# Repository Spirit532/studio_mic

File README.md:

<div align="right">
  <details>
    <summary >🌐 Language</summary>
    <div>
      <div align="center">
        <a href="https://openaitx.github.io/view.html?user=Spirit532&project=studio_mic&lang=en">English</a>
        | <a href="https://openaitx.github.io/view.html?user=Spirit532&project=studio_mic&lang=zh-CN">简体中文</a>
        | <a href="https://openaitx.github.io/view.html?user=Spirit532&project=studio_mic&lang=zh-TW">繁體中文</a>
        | <a href="https://openaitx.github.io/view.html?user=Spirit532&project=studio_mic&lang=ja">日本語</a>
        | <a href="https://openaitx.github.io/view.html?user=Spirit532&project=studio_mic&lang=ko">한국어</a>
        | <a href="https://openaitx.github.io/view.html?user=Spirit532&project=studio_mic&lang=hi">हिन्दी</a>
        | <a href="https://openaitx.github.io/view.html?user=Spirit532&project=studio_mic&lang=th">ไทย</a>
        | <a href="https://openaitx.github.io/view.html?user=Spirit532&project=studio_mic&lang=fr">Français</a>
        | <a href="https://openaitx.github.io/view.html?user=Spirit532&project=studio_mic&lang=de">Deutsch</a>
        | <a href="https://openaitx.github.io/view.html?user=Spirit532&project=studio_mic&lang=es">Español</a>
        | <a href="https://openaitx.github.io/view.html?user=Spirit532&project=studio_mic&lang=it">Italiano</a>
        | <a href="https://openaitx.github.io/view.html?user=Spirit532&project=studio_mic&lang=ru">Русский</a>
        | <a href="https://openaitx.github.io/view.html?user=Spirit532&project=studio_mic&lang=pt">Português</a>
        | <a href="https://openaitx.github.io/view.html?user=Spirit532&project=studio_mic&lang=nl">Nederlands</a>
        | <a href="https://openaitx.github.io/view.html?user=Spirit532&project=studio_mic&lang=pl">Polski</a>
        | <a href="https://openaitx.github.io/view.html?user=Spirit532&project=studio_mic&lang=ar">العربية</a>
        | <a href="https://openaitx.github.io/view.html?user=Spirit532&project=studio_mic&lang=fa">فارسی</a>
        | <a href="https://openaitx.github.io/view.html?user=Spirit532&project=studio_mic&lang=tr">Türkçe</a>
        | <a href="https://openaitx.github.io/view.html?user=Spirit532&project=studio_mic&lang=vi">Tiếng Việt</a>
        | <a href="https://openaitx.github.io/view.html?user=Spirit532&project=studio_mic&lang=id">Bahasa Indonesia</a>
        | <a href="https://openaitx.github.io/view.html?user=Spirit532&project=studio_mic&lang=as">অসমীয়া</
      </div>
    </div>
  </details>
</div>

# Simple, high quality condenser microphone for under $100

I needed a good quality microphone, but all of the options available were either a bit pricy or just not really good in performance, so I decided to build my own.

The microphone build uses a clone RK12/CK12 capsule($40-50 on Aliexpress/Ebay/etc, search for "edge terminated capsule"), a U87 donor body($15-30, also Aliexpress, search term "U87 mic"), and a custom preamp board($20-30, this project).

The board is very simple, yet high performance - it uses a dual FET input opamp in a single package to both convert the capsule's impedance and provide a differential signal, while the bias is provided by a slightly cursed hex schmitt trigger inverter charge pump.

With the setup pictured below, the results are, to the non-audiophool ear, perfect. There is practically no self-noise due to the simplicity of the circuit and performance of the chosen opamp, plenty of dynamic range, and no signal distortion/"coloration". You get exactly what the capsule sees on the XLR connector.

#### Notes about component choice
  1. You can use pretty much any FET input opamp, **however** you must pay close attention to the quiescent current. This circuit uses a fairly high impedance power path, and the phantom power standard can't provide much current in the first place. Total power consumption of the two opamps should be no more than ~7-8mA(3.5-4mA per).

  2. Same goes for the hex inverter in terms of power consumption, but otherwise anything will do. You can substitute the part with any 40106 clone of similar functionality.
  
  3. Take care to purchase high voltage rated capacitors where specified - this is important! Ceramic capacitors lose capacitance at higher voltages, so X7R class caps rated at 100V or more are preferred(this won't explicitly solve derating, but it will help). All values are  readily available in 0805 size, so it's not an issue.

  4. Choose NP0/C0G capacitors for ceramics if your budget allows. They'll improve performance a little bit, but not by a whole lot. (this will solve derating, but at significant cost)
  
The design is licensed under the MIT license. If you want to build it, go ahead. If you want to sell it, also go ahead, but just mention this page or something. Pretty much none of this is really original and has been done dozens of times(i.e. DJJules/Sound Sleuth over at Instructables, whose circuit I took inspiration from), I just put my own twist on it.

#### Important note about cheap donor bodies
Most cheap donor bodies will come pre-anodized or even pre-painted, including contact surfaces at separation points(circuit cover, headbasket, nut, spacers, etc), __make sure to sand them down__ to expose metal, or you'll pick up tons of mains hum and other external electrical noise!

## Get the board
If you can't make or assemble the board yourself... well, uh, good luck, but most assembly houses in China will happily make them for you for not very much money.
I had a PCBWay affiliate link here, but I wouldn't recommend dealing with them anymore.

## Schematic
(also available as pdf or KiCad 7 sources, see files)

## PCB render

## Assembled board, DIY single-layer version(homemade)

## Capsule mounted in the donor body

## U87 clone donor body

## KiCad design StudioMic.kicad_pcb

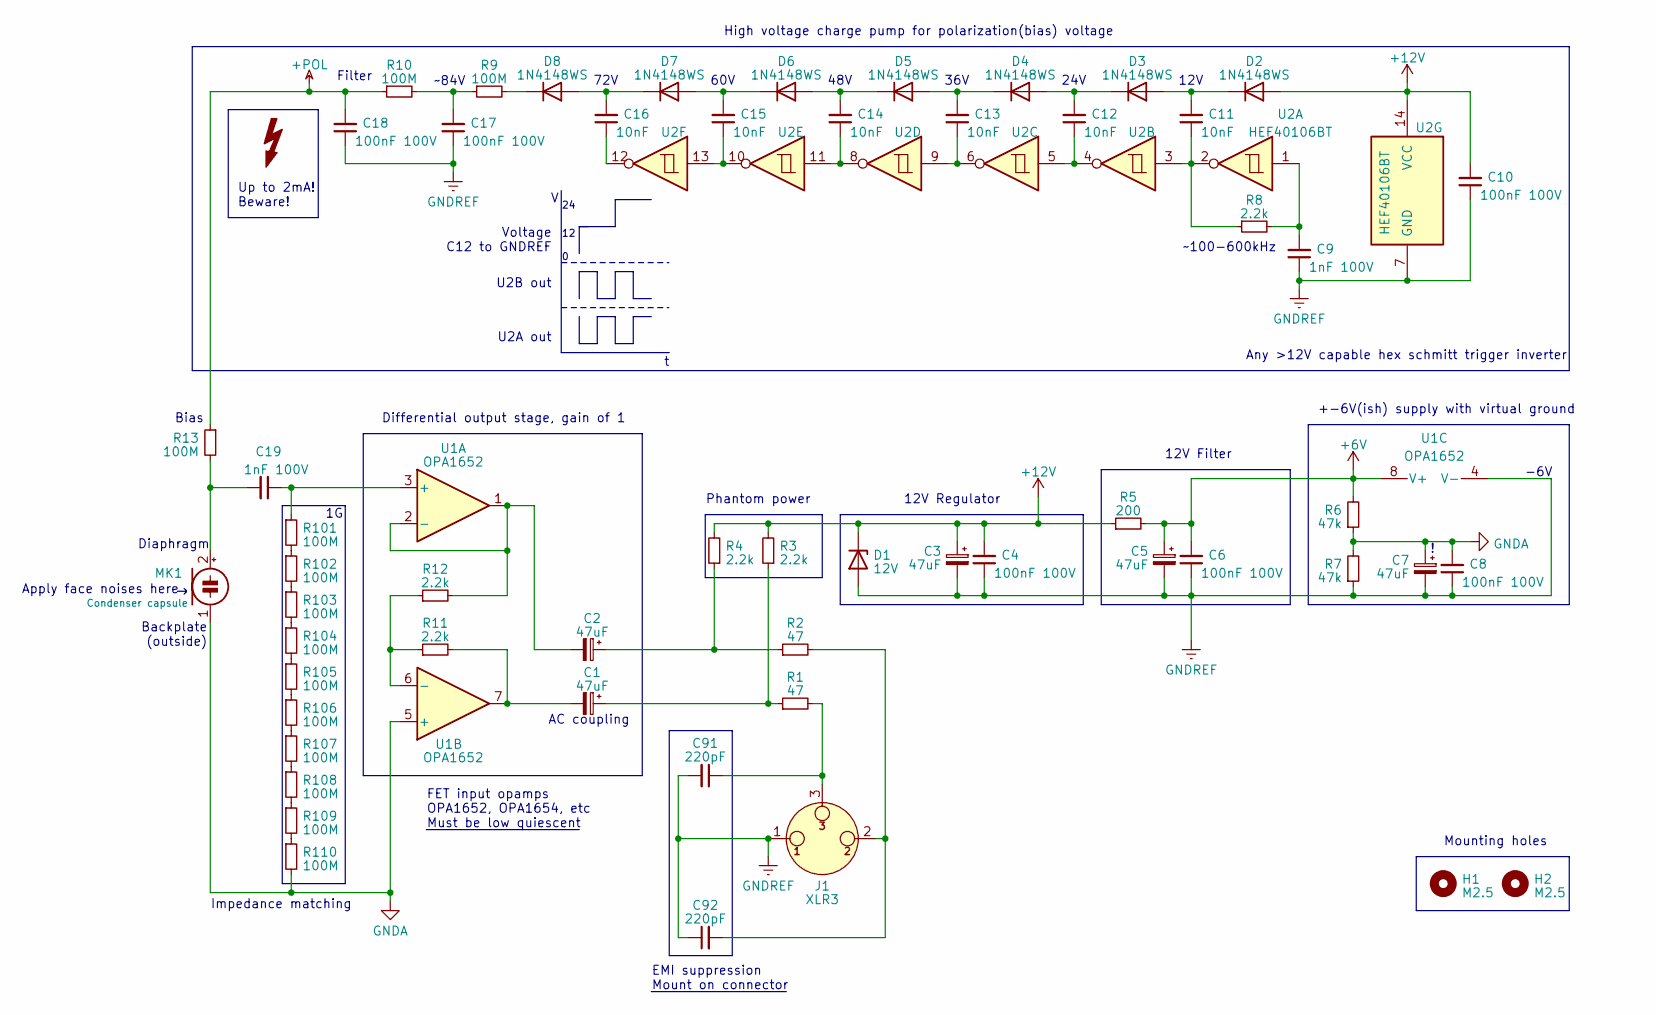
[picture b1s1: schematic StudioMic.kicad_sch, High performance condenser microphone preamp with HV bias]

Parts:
C1, C2, C3, C5, C7: 47uF; CP_Elec_8x10.5
C4, C6, C8, C10, C17, C18: 100nF 100V; C_0805_2012Metric
C9, C19: 1nF 100V; C_0805_2012Metric
C11, C12, C13, C14, C15, C16: 10nF; C_0805_2012Metric
C91, C92: 220pF
D1: 12V; D_MiniMELF_Handsoldering
D2, D3, D4, D5, D6, D7, D8: 1N4148WS; D_SOD-323_HandSoldering
H1, H2: M2.5; MountingHole_2.7mm_M2.5_ISO14580
J1: XLR3; Pads_3pin_10mm
MK1: Condenser capsule; Pads_2pin_10mm
R1, R2: 47; R_0805_2012Metric
R3, R4, R8, R11, R12: 2.2k; R_0805_2012Metric
R5: 200; R_0805_2012Metric
R6, R7: 47k; R_0805_2012Metric
R9, R10, R13, R101, R102, R103, R104, R105, R106, R107, R108, R109, R110: 100M; R_0805_2012Metric
U1: OPA1652; SOIC-8_3.9x4.9mm_P1.27mm
U2: HEF40106BT; SO-14_3.9x8.65mm_P1.27mm

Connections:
+6V: C5.1, C6.2, R5.2, R6.2, U1.8 (V+)
+12V: C3.1, C4.2, C10.2, D1.1 (K), D2.2 (A), R3.2, R4.2, R5.1, U2.14 (VCC)
GNDA: C7.1, C8.2, MK1.1 (-), R6.1, R7.2, R110.2, U1.5 (+)
GNDREF: C3.2, C4.1, C5.2, C6.1, C7.2, C8.1, C9.1, C10.1, C17.1, C18.1, C91.2, C92.1, D1.2 (A), J1.1, R7.1, U1.4 (V-), U2.7 (GND)
HT: C18.2, R10.1, R13.1
unnamed: C1.1, R1.1, R3.1
unnamed: C1.2, R11.2, U1.7
unnamed: C2.1, R2.1, R4.1
unnamed: C9.2, R8.2, U2.1
unnamed: C11.1, R8.1, U2.2, U2.3
unnamed: C12.1, U2.4, U2.5
unnamed: C13.1, U2.6, U2.9
unnamed: C14.1, U2.8, U2.11
unnamed: C15.1, U2.10, U2.13
unnamed: C16.1, U2.12
unnamed: C17.2, R9.1, R10.2
unnamed: C91.1, J1.3, R1.2
unnamed: C92.2, J1.2, R2.2
unnamed: C11.2, D2.1 (K), D3.2 (A)
unnamed: C12.2, D3.1 (K), D4.2 (A)
unnamed: C13.2, D4.1 (K), D5.2 (A)
unnamed: C14.2, D5.1 (K), D6.2 (A)
unnamed: C15.2, D6.1 (K), D7.2 (A)
unnamed: C16.2, D7.1 (K), D8.2 (A)
unnamed: D8.1 (K), R9.2
unnamed: C19.2, MK1.2 (+), R13.2
unnamed: R101.2, R102.1
unnamed: R102.2, R103.1
unnamed: R103.2, R104.1
unnamed: R104.2, R105.1
unnamed: R105.2, R106.1
unnamed: R106.2, R107.1
unnamed: R107.2, R108.1
unnamed: R108.2, R109.1
unnamed: R109.2, R110.1
unnamed: C19.1, R101.1, U1.3 (+)
unnamed: C2.2, R12.2, U1.1, U1.2 (-)
unnamed: R11.1, R12.1, U1.6 (-)

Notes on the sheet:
12V
Phantom power
Impedance matching
60V
Filter
Bias
Up to 2mA! Beware!
Mounting holes
EMI suppression Mount on connector
FET input opamps OPA1652, OPA1654, etc Must be low quiescent
36V
-6V
24V
Voltage C12 to GNDREF
Differential output stage, gain of 1
12V Regulator
12V Filter
~84V
~100-600kHz
U2A out
U2B out
48V
Any >12V capable hex schmitt trigger inverter
Backplate (outside)
+-6V(ish) supply with virtual ground
AC coupling
Diaphragm
Apply face noises here
High voltage charge pump for polarization(bias) voltage
72V

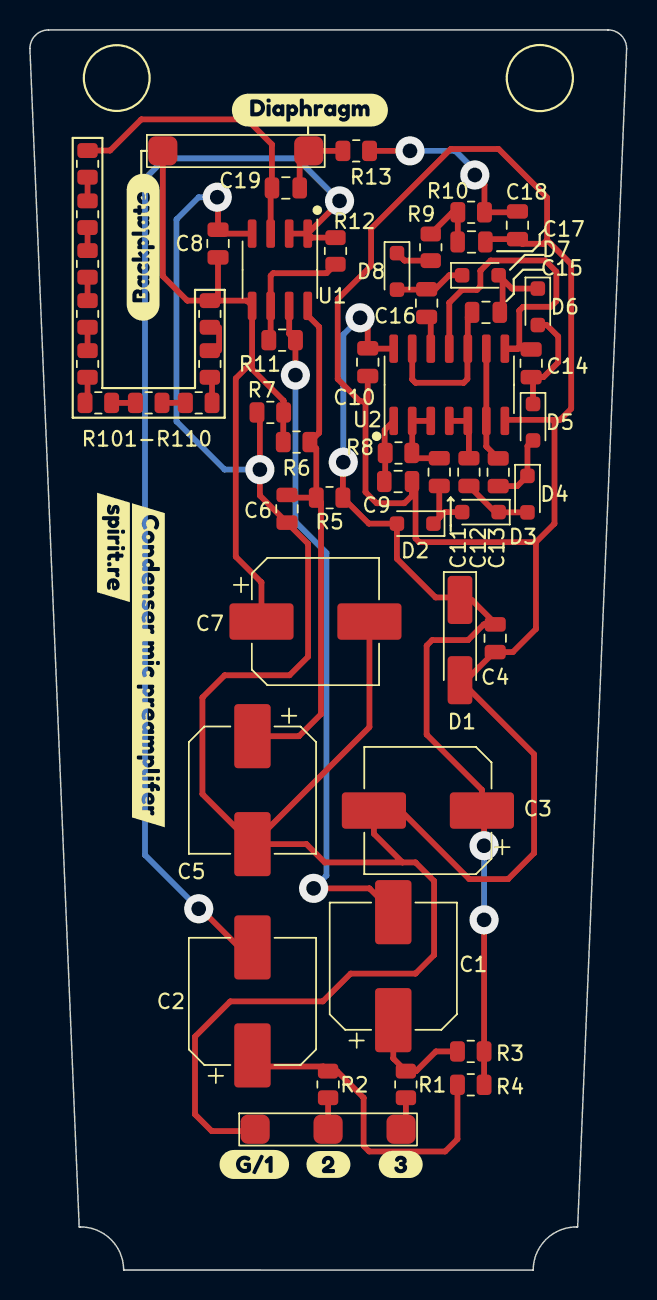
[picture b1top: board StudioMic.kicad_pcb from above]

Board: 2 copper layers, 40.9 x 85.0 mm, 63 parts (0 on the bottom side), 38 nets.

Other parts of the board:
kibuzzard-64153C1C: G***; kibuzzard-64153C1C
kibuzzard-64153C31: G***; kibuzzard-64153C31
kibuzzard-640955D5: G***; kibuzzard-640955D5
kibuzzard-640955DC: G***; kibuzzard-640955DC
kibuzzard-640955F0: G***; kibuzzard-640955F0
kibuzzard-6409565D: G***; kibuzzard-6409565D
kibuzzard-64095693: G***; kibuzzard-64095693

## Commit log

2023-03-18 Initial upload
    All the stuff
2023-03-19 Forgot to mention some inspiration, have to be fair
2023-03-19 Note about body
2023-03-19 Search terms for DIY
2023-04-11 Missed a spot
2026-04-05 Auto-translate README and Wiki
